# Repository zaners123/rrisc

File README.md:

# RRISC (Reduced Reduced Instruction Set Computer)

My primary goal for this project was to make a computer from "scratch"
(simple logic gates and memory, no embedded microcontrollers/FPGAs/etc) to learn more about Computer Engineering
as a "learn by doing" approach.

Since it's only made out of simple logic gates and hand-soldered, it needs to be simple in design
(no microcode/pipelining) and in implementation (trying to aim for around 50 logic chips,
none of which are more complex than a comparator).

This project includes the Assembler, LogiSim simulator/emulator, schematic, and PCB.
This is the computer at every level of abstraction, and as such this is Open Source Hardware.

## What is RISC? What does this computer do? 

A RISC computer commonly has simple operations to have higher instructions per second.
My computer has extremely simple operations to have extreme efficiency (ideally).
My goal for this computer is for it to run at about 20MHz.

This is a General Purpose Von-Neumann-Architecture computer with 8-bit instructions.
It has 64Kb of RAM and all 16 instructions follow a quick 3-stage IF/EX/WB cycle.

Instructions are broken up into two parts. Here's the entire **Instruction Set Architecture**:

 ID | Opcode |  Description           |  Argument Type
----|--------|------------------------|-------------------------
 _  | 4 bits | _                      | 4 bits
0x0 | ADD    | Add to R0              | Register(1)
0x1 | ADDI   | Add to R0              | Immediate(2)       
0x2 | SUB    | Subtract from R0       | Register(1)   
0x3 | SUBI   | Subtract from R0       | Immediate(2)  
0x4 | SKIP   | Skip next instruction  | Condition(3)  
0x5 | JUMP   | Jump to MEM            | Condition(3)  
0x6 | XOR    | Xor                    | Register(1)        
0x7 | XORI   | Xor                    | Immediate(2)       
0x8 | AND    | And                    | Register(1)        
0x9 | ANDI   | And                    | Immediate(2)       
0xA | SET    | Move ACC to Reg        | Register(1)
0xB | RB     | Read from memory to Reg| Register(1)
0xC | GET    | Move Reg to ACC        | Register(1)
0xD | WB     | Write from reg to memory|Register(1)
0xE | OR     |                        |
0xF | ORI    |                        |

## Register(1)
The last 4 bits of this argument point to one of the 16 registers.

ACC (AKA R0) is the accumulator register.

R1-RC General Purpose Registers.

RMH,RML point in memory (Register Memory High, Register Memory Low).

RCMP is used in conditional operations<sup>[3](3)</sup>

## Immediate(2)

## Condition(3)

# Assembler

Given an assembly file (Ex: code.asm), it turns it into a hex file (Ex: code.asm.hex) that can be loaded either onto
the real computer, or the simulated computer in LogiSim.

# Simulation

This represents the computer's overall layout. It is both a logical diagram for the computer and a convenient simulator for programs.

Open this with Logisim Evolution. I use "logisim-evolution-3.4.1-all.jar".
Upload the hex from the assembler into the RAM, start the controller, and watch it run!

# Hardware

The strict hardware requirement of this computer is that everything except the memory-mapped-IO has to be made from 7400 logic.

This is made in KiCad, and contains the schematic (local layout of how things connect)
and the PCB design (how to physically connect everything together).

The plan is to have the submodules used in LogiSim (registers, ALU, RAM, etc) be a daughter board for the main PCB.

The plan is to design/order/build the PCBs in this order:
1. Program Counter
    - Logic for jump/skip decisions
2. Registers
    - Might use either a literal register file (select MUX, asynchronous D-latch, 8x 16:1 demux) or a 74xx register file 
3. ALU
4. RAM/ROM/Programmer
5. Motherboard/Controller
6. Memory-Mapped IO
    - Memory Mapped UART
    - Memory Mapped 7-segment Display

This way, I can test them all separately, and revisions can be made more easily.

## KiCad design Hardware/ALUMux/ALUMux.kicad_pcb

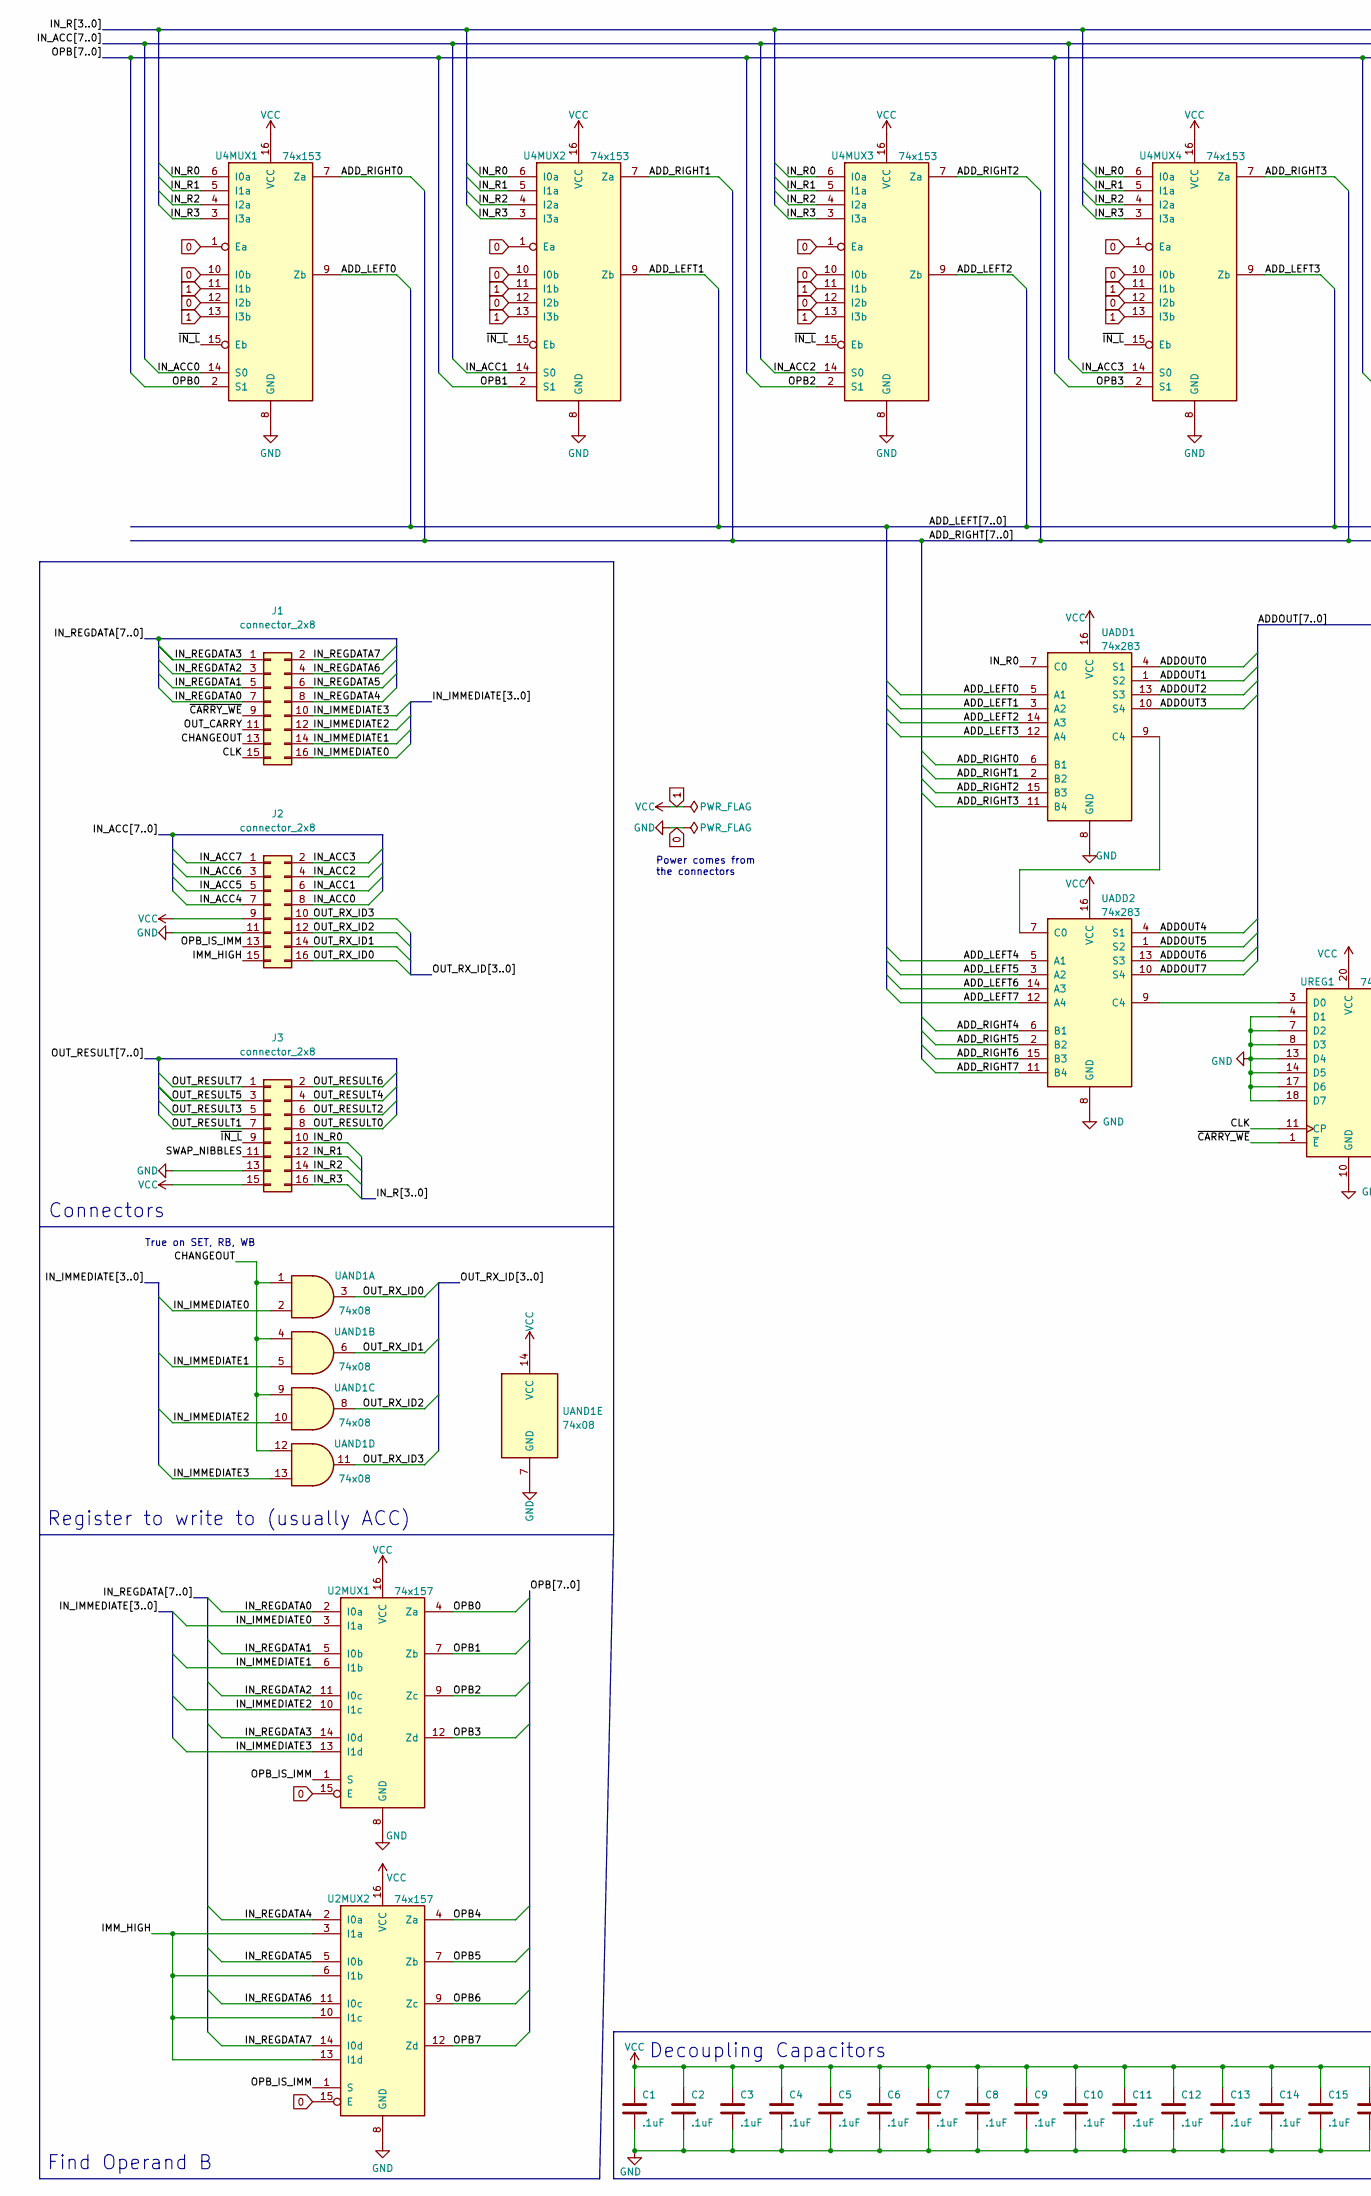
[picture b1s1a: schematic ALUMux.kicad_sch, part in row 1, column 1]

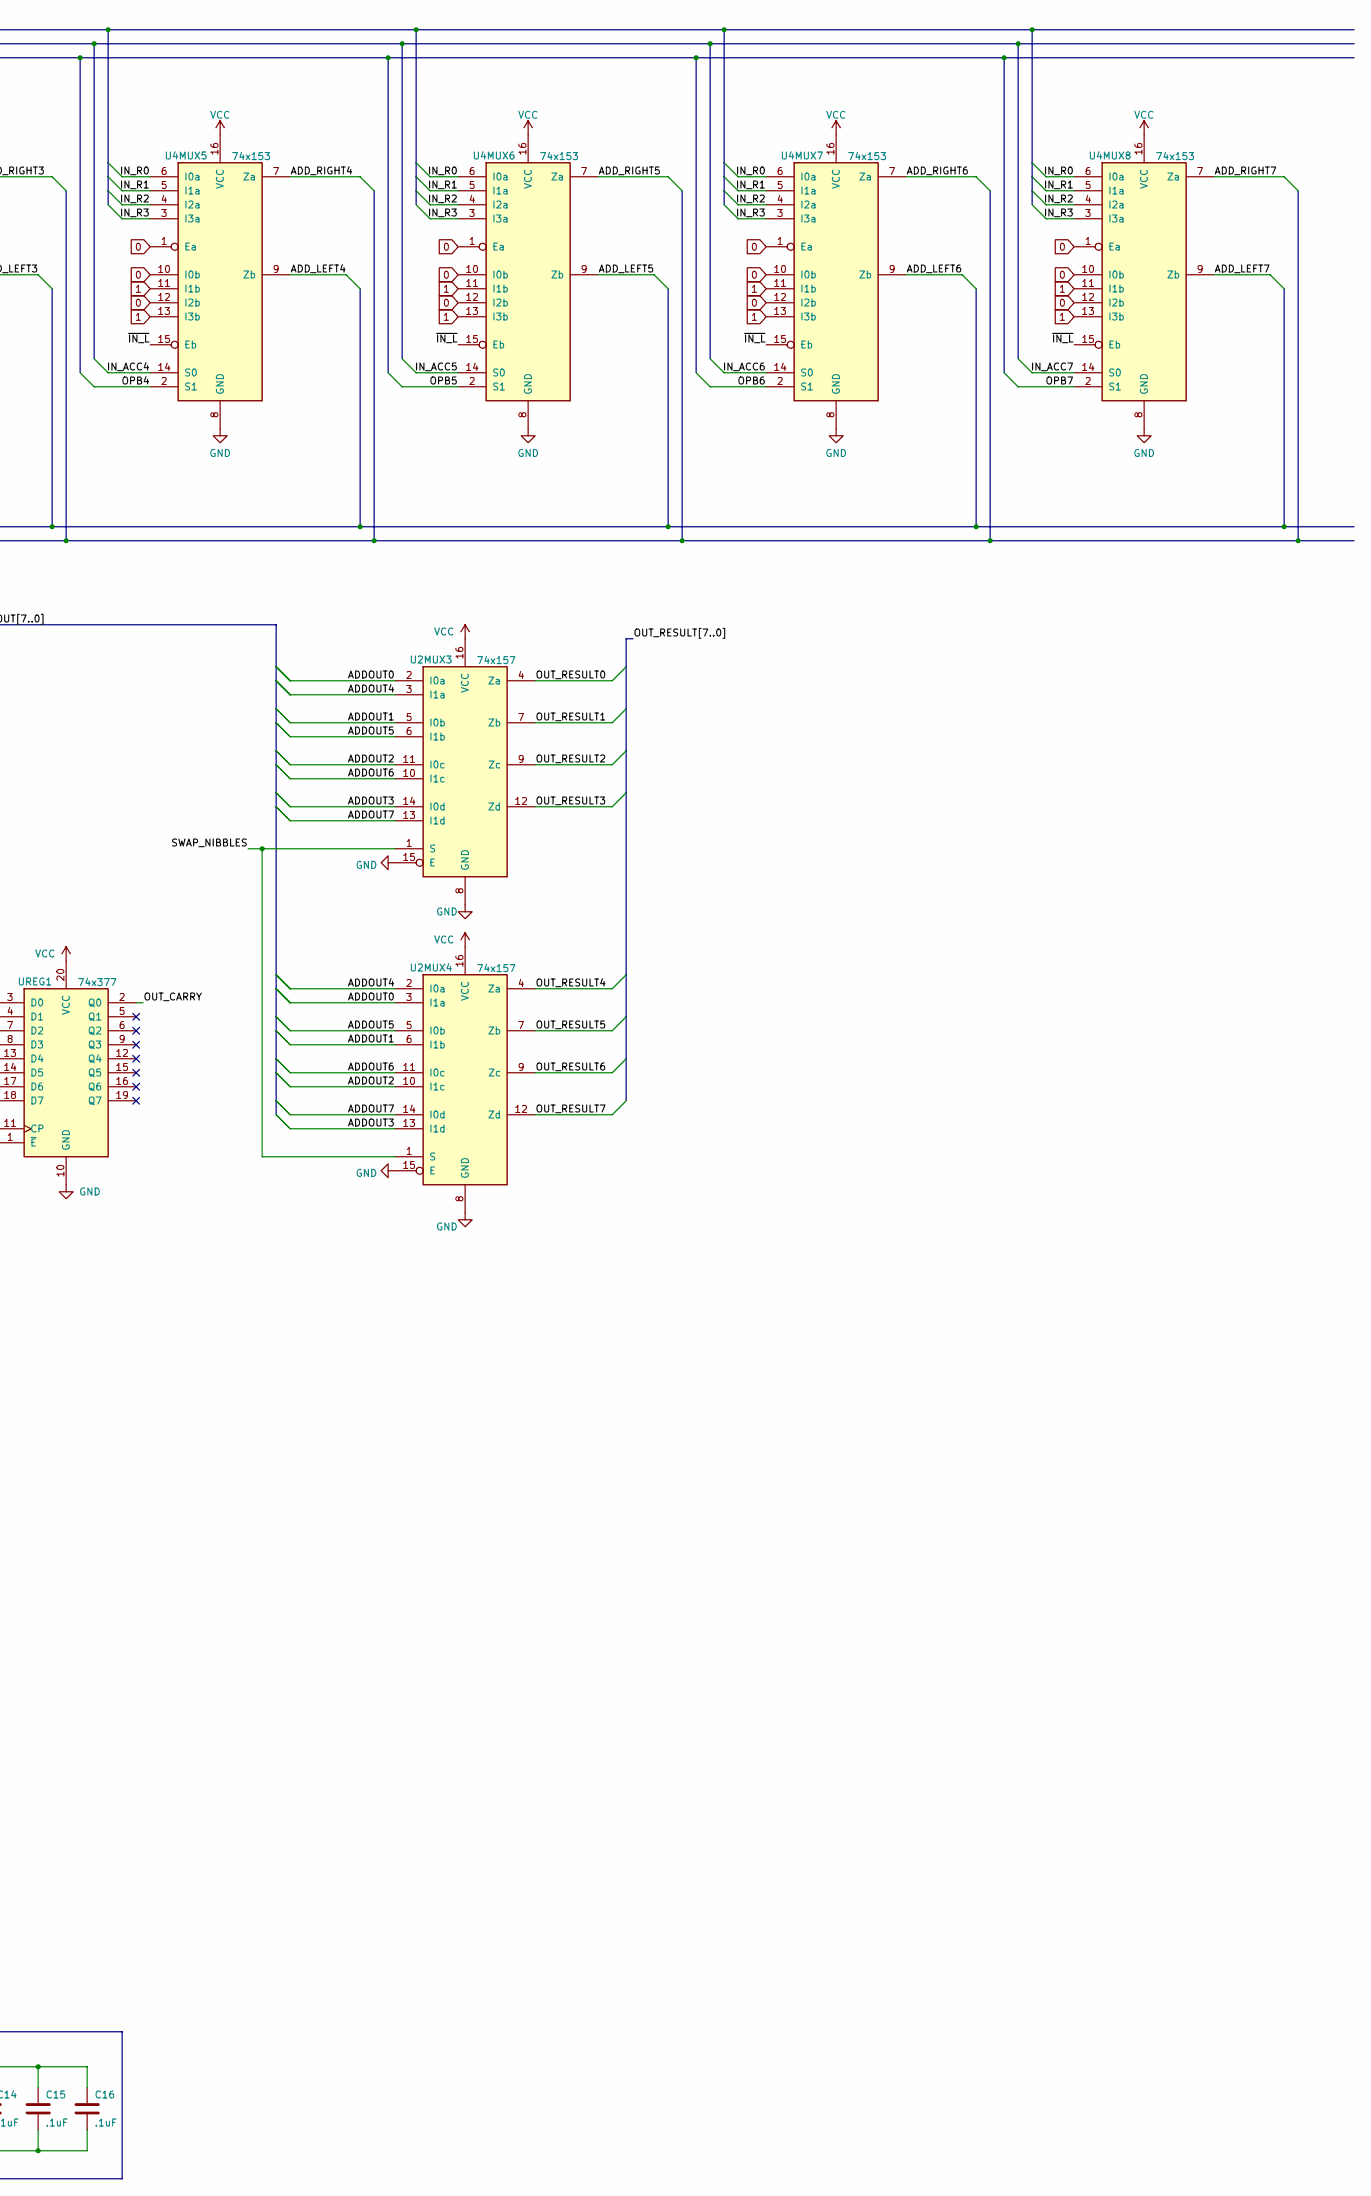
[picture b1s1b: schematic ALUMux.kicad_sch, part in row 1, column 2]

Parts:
C1, C2, C3, C4, C5, C6, C7, C8, C9, C10, C11, C12, C13, C14, C15, C16: .1uF; C_1206_3216Metric_Pad1.33x1.80mm_HandSolder
J1, J2, J3: connector_2x8; PinHeader_2x08_P2.54mm_Horizontal
U2MUX1, U2MUX2, U2MUX3, U2MUX4: 74x157; D_R-PDSO-G16
U4MUX1, U4MUX2, U4MUX3, U4MUX4, U4MUX5, U4MUX6, U4MUX7, U4MUX8: 74x153; D_R-PDSO-G16
UADD1, UADD2: 74x283; D_R-PDSO-G16
UAND1: 74x08; D_R-PDSO-G14
UREG1: 74x377; ON-SOIC20-WB

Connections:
0: C1.2, C2.2, C3.2, C4.2, C5.2, C6.2, C7.2, C8.2, C9.2, C10.2, C11.2, C12.2, C13.2, C14.2, C15.2, C16.2, J2.11, J3.13, U2MUX1.8 (GND), U2MUX1.15 (E), U2MUX2.8 (GND), U2MUX2.15 (E), U2MUX3.8 (GND), U2MUX3.15 (E), U2MUX4.8 (GND), U2MUX4.15 (E), U4MUX1.1 (Ea), U4MUX1.8 (GND), U4MUX1.10 (I0b), U4MUX1.12 (I2b), U4MUX2.1 (Ea), U4MUX2.8 (GND), U4MUX2.10 (I0b), U4MUX2.12 (I2b), U4MUX3.1 (Ea), U4MUX3.8 (GND), U4MUX3.10 (I0b), U4MUX3.12 (I2b), U4MUX4.1 (Ea), U4MUX4.8 (GND), U4MUX4.10 (I0b), U4MUX4.12 (I2b), U4MUX5.1 (Ea), U4MUX5.8 (GND), U4MUX5.10 (I0b), U4MUX5.12 (I2b), U4MUX6.1 (Ea), U4MUX6.8 (GND), U4MUX6.10 (I0b), U4MUX6.12 (I2b), U4MUX7.1 (Ea), U4MUX7.8 (GND), U4MUX7.10 (I0b), U4MUX7.12 (I2b), U4MUX8.1 (Ea), U4MUX8.8 (GND), U4MUX8.10 (I0b), U4MUX8.12 (I2b), UADD1.8 (GND), UADD2.8 (GND), UAND1.7 (GND), UREG1.4 (D1), UREG1.7 (D2), UREG1.8 (D3), UREG1.10 (GND), UREG1.13 (D4), UREG1.14 (D5), UREG1.17 (D6), UREG1.18 (D7)
1: C1.1, C2.1, C3.1, C4.1, C5.1, C6.1, C7.1, C8.1, C9.1, C10.1, C11.1, C12.1, C13.1, C14.1, C15.1, C16.1, J2.9, J3.15, U2MUX1.16 (VCC), U2MUX2.16 (VCC), U2MUX3.16 (VCC), U2MUX4.16 (VCC), U4MUX1.11 (I1b), U4MUX1.13 (I3b), U4MUX1.16 (VCC), U4MUX2.11 (I1b), U4MUX2.13 (I3b), U4MUX2.16 (VCC), U4MUX3.11 (I1b), U4MUX3.13 (I3b), U4MUX3.16 (VCC), U4MUX4.11 (I1b), U4MUX4.13 (I3b), U4MUX4.16 (VCC), U4MUX5.11 (I1b), U4MUX5.13 (I3b), U4MUX5.16 (VCC), U4MUX6.11 (I1b), U4MUX6.13 (I3b), U4MUX6.16 (VCC), U4MUX7.11 (I1b), U4MUX7.13 (I3b), U4MUX7.16 (VCC), U4MUX8.11 (I1b), U4MUX8.13 (I3b), U4MUX8.16 (VCC), UADD1.16 (VCC), UADD2.16 (VCC), UAND1.14 (VCC), UREG1.20 (VCC)
/ADDOUT0: U2MUX3.2 (I0a), U2MUX4.3 (I1a), UADD1.4 (S1)
/ADDOUT1: U2MUX3.5 (I0b), U2MUX4.6 (I1b), UADD1.1 (S2)
/ADDOUT2: U2MUX3.11 (I0c), U2MUX4.10 (I1c), UADD1.13 (S3)
/ADDOUT3: U2MUX3.14 (I0d), U2MUX4.13 (I1d), UADD1.10 (S4)
/ADDOUT4: U2MUX3.3 (I1a), U2MUX4.2 (I0a), UADD2.4 (S1)
/ADDOUT5: U2MUX3.6 (I1b), U2MUX4.5 (I0b), UADD2.1 (S2)
/ADDOUT6: U2MUX3.10 (I1c), U2MUX4.11 (I0c), UADD2.13 (S3)
/ADDOUT7: U2MUX3.13 (I1d), U2MUX4.14 (I0d), UADD2.10 (S4)
/ADD_LEFT0: U4MUX1.9 (Zb), UADD1.5 (A1)
/ADD_LEFT1: U4MUX2.9 (Zb), UADD1.3 (A2)
/ADD_LEFT2: U4MUX3.9 (Zb), UADD1.14 (A3)
/ADD_LEFT3: U4MUX4.9 (Zb), UADD1.12 (A4)
/ADD_LEFT4: U4MUX5.9 (Zb), UADD2.5 (A1)
/ADD_LEFT5: U4MUX6.9 (Zb), UADD2.3 (A2)
/ADD_LEFT6: U4MUX7.9 (Zb), UADD2.14 (A3)
/ADD_LEFT7: U4MUX8.9 (Zb), UADD2.12 (A4)
/ADD_RIGHT0: U4MUX1.7 (Za), UADD1.6 (B1)
/ADD_RIGHT1: U4MUX2.7 (Za), UADD1.2 (B2)
/ADD_RIGHT2: U4MUX3.7 (Za), UADD1.15 (B3)
/ADD_RIGHT3: U4MUX4.7 (Za), UADD1.11 (B4)
/ADD_RIGHT4: U4MUX5.7 (Za), UADD2.6 (B1)
/ADD_RIGHT5: U4MUX6.7 (Za), UADD2.2 (B2)
/ADD_RIGHT6: U4MUX7.7 (Za), UADD2.15 (B3)
/ADD_RIGHT7: U4MUX8.7 (Za), UADD2.11 (B4)
/CHANGEOUT: J1.13, UAND1.1, UAND1.4, UAND1.9, UAND1.12
/CLK: J1.15, UREG1.11 (CP)
/IMM_HIGH: J2.15, U2MUX2.3 (I1a), U2MUX2.6 (I1b), U2MUX2.10 (I1c), U2MUX2.13 (I1d)
/IN_ACC0: J2.8, U4MUX1.14 (S0)
/IN_ACC1: J2.6, U4MUX2.14 (S0)
/IN_ACC2: J2.4, U4MUX3.14 (S0)
/IN_ACC3: J2.2, U4MUX4.14 (S0)
/IN_ACC4: J2.7, U4MUX5.14 (S0)
/IN_ACC5: J2.5, U4MUX6.14 (S0)
/IN_ACC6: J2.3, U4MUX7.14 (S0)
/IN_ACC7: J2.1, U4MUX8.14 (S0)
/IN_IMMEDIATE0: J1.16, U2MUX1.3 (I1a), UAND1.2
/IN_IMMEDIATE1: J1.14, U2MUX1.6 (I1b), UAND1.5
/IN_IMMEDIATE2: J1.12, U2MUX1.10 (I1c), UAND1.10
/IN_IMMEDIATE3: J1.10, U2MUX1.13 (I1d), UAND1.13
/IN_R0: J3.10, U4MUX1.6 (I0a), U4MUX2.6 (I0a), U4MUX3.6 (I0a), U4MUX4.6 (I0a), U4MUX5.6 (I0a), U4MUX6.6 (I0a), U4MUX7.6 (I0a), U4MUX8.6 (I0a), UADD1.7 (C0)
/IN_R1: J3.12, U4MUX1.5 (I1a), U4MUX2.5 (I1a), U4MUX3.5 (I1a), U4MUX4.5 (I1a), U4MUX5.5 (I1a), U4MUX6.5 (I1a), U4MUX7.5 (I1a), U4MUX8.5 (I1a)
/IN_R2: J3.14, U4MUX1.4 (I2a), U4MUX2.4 (I2a), U4MUX3.4 (I2a), U4MUX4.4 (I2a), U4MUX5.4 (I2a), U4MUX6.4 (I2a), U4MUX7.4 (I2a), U4MUX8.4 (I2a)
/IN_R3: J3.16, U4MUX1.3 (I3a), U4MUX2.3 (I3a), U4MUX3.3 (I3a), U4MUX4.3 (I3a), U4MUX5.3 (I3a), U4MUX6.3 (I3a), U4MUX7.3 (I3a), U4MUX8.3 (I3a)
/IN_REGDATA0: J1.7, U2MUX1.2 (I0a)
/IN_REGDATA1: J1.5, U2MUX1.5 (I0b)
/IN_REGDATA2: J1.3, U2MUX1.11 (I0c)
/IN_REGDATA3: J1.1, U2MUX1.14 (I0d)
/IN_REGDATA4: J1.8, U2MUX2.2 (I0a)
/IN_REGDATA5: J1.6, U2MUX2.5 (I0b)
/IN_REGDATA6: J1.4, U2MUX2.11 (I0c)
/IN_REGDATA7: J1.2, U2MUX2.14 (I0d)
/OPB0: U2MUX1.4 (Za), U4MUX1.2 (S1)
/OPB1: U2MUX1.7 (Zb), U4MUX2.2 (S1)
/OPB2: U2MUX1.9 (Zc), U4MUX3.2 (S1)
/OPB3: U2MUX1.12 (Zd), U4MUX4.2 (S1)
/OPB4: U2MUX2.4 (Za), U4MUX5.2 (S1)
/OPB5: U2MUX2.7 (Zb), U4MUX6.2 (S1)
/OPB6: U2MUX2.9 (Zc), U4MUX7.2 (S1)
/OPB7: U2MUX2.12 (Zd), U4MUX8.2 (S1)
/OPB_IS_IMM: J2.13, U2MUX1.1 (S), U2MUX2.1 (S)
/OUT_CARRY: J1.11, UREG1.2 (Q0)
/OUT_RESULT0: J3.8, U2MUX3.4 (Za)
/OUT_RESULT1: J3.7, U2MUX3.7 (Zb)
/OUT_RESULT2: J3.6, U2MUX3.9 (Zc)
/OUT_RESULT3: J3.5, U2MUX3.12 (Zd)
/OUT_RESULT4: J3.4, U2MUX4.4 (Za)
/OUT_RESULT5: J3.3, U2MUX4.7 (Zb)
/OUT_RESULT6: J3.2, U2MUX4.9 (Zc)
/OUT_RESULT7: J3.1, U2MUX4.12 (Zd)
/OUT_RX_ID0: J2.16, UAND1.3
/OUT_RX_ID1: J2.14, UAND1.6
/OUT_RX_ID2: J2.12, UAND1.8
/OUT_RX_ID3: J2.10, UAND1.11
/SWAP_NIBBLES: J3.11, U2MUX3.1 (S), U2MUX4.1 (S)
/~CARRY_WE: J1.9, UREG1.1 (~E)
/~IN_L: J3.9, U4MUX1.15 (Eb), U4MUX2.15 (Eb), U4MUX3.15 (Eb), U4MUX4.15 (Eb), U4MUX5.15 (Eb), U4MUX6.15 (Eb), U4MUX7.15 (Eb), U4MUX8.15 (Eb)
unnamed: UADD1.9 (C4), UADD2.7 (C0)
unnamed: UADD2.9 (C4), UREG1.3 (D0)

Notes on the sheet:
Connectors
True on SET, RB, WB
Register to write to (usually ACC)
Power comes from the connectors
Find Operand B
Decoupling Capacitors

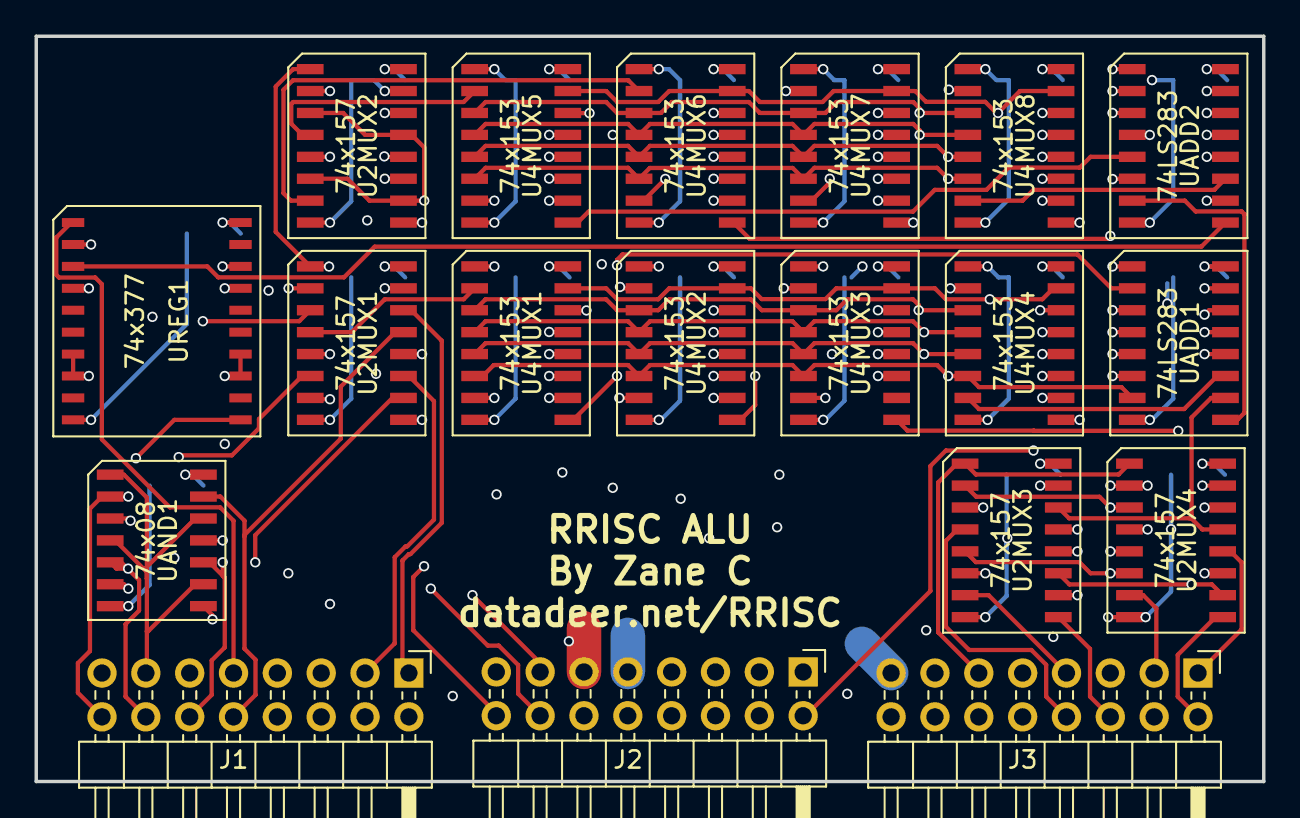
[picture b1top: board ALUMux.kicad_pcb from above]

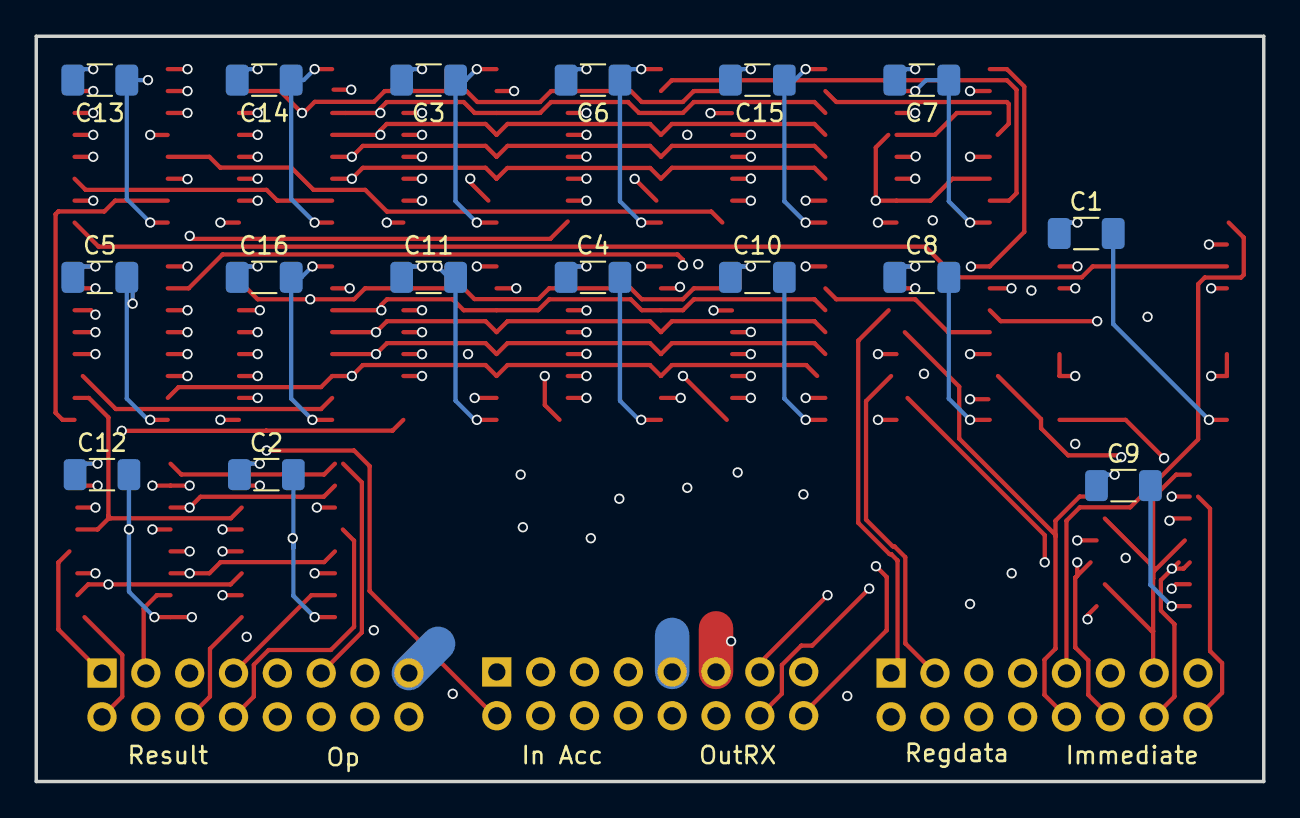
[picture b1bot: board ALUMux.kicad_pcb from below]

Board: 4 copper layers, 71.1 x 43.2 mm, 35 parts (16 on the bottom side), 80 nets.

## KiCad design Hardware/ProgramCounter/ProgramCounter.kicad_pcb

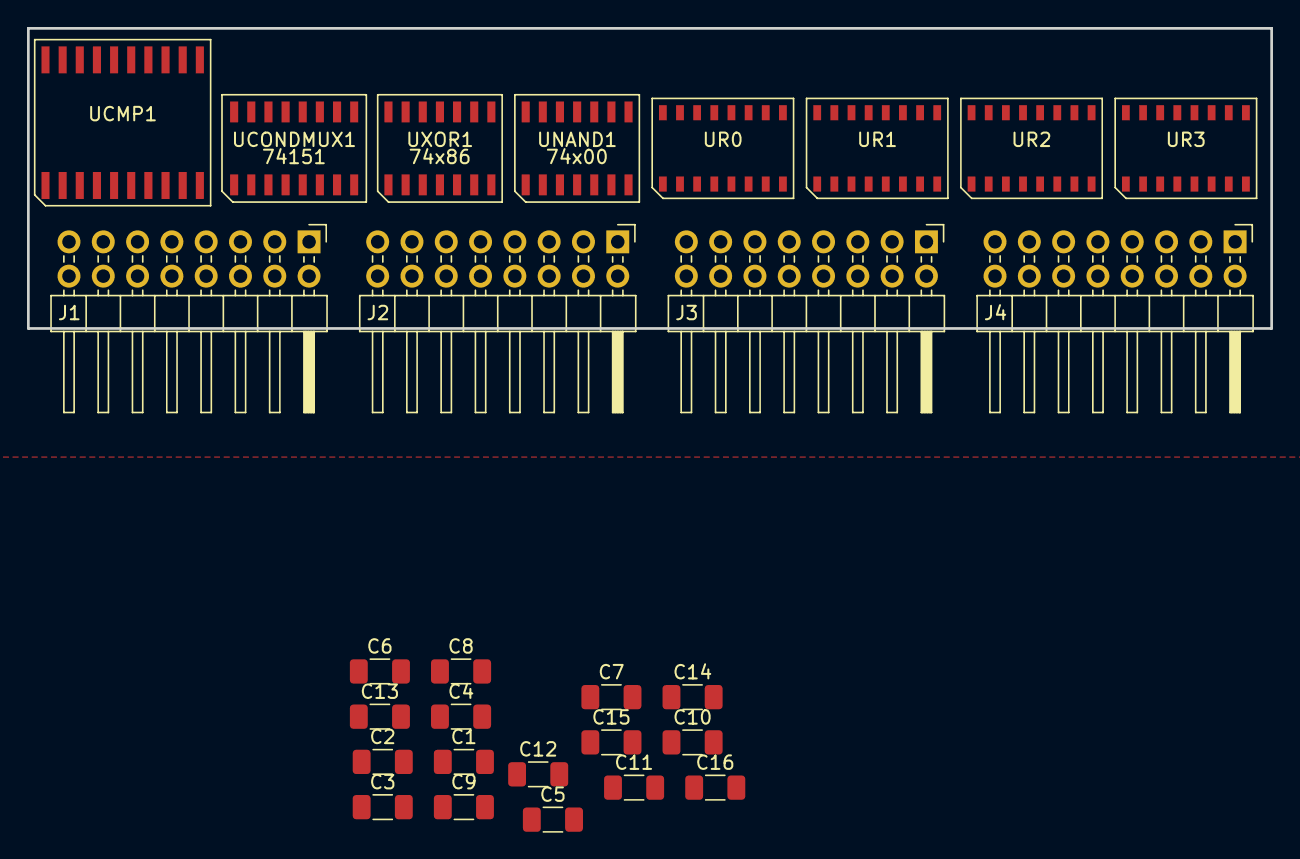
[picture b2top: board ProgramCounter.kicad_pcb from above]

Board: 4 copper layers, 92.1 x 22.2 mm, 28 parts (0 on the bottom side), 70 nets, no tracks yet.

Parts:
C1, C2, C3, C4, C5, C6, C7, C8, C9, C10, C11, C12, C13, C14, C15, C16: .1uF; C_1206_3216Metric_Pad1.33x1.80mm_HandSolder
J1, J2, J3, J4: Conn_02x08; PinHeader_2x08_P2.54mm_Horizontal
UCMP1: 74LS684; SOIC20_TI_DW0020A
UCONDMUX1: 74151; D_R-PDSO-G16
UNAND1: 74x00; D_R-PDSO-G14
UR0, UR1, UR2, UR3: 74LS161; SOIC16-ONSEMI_751B-05_K
UXOR1: 74x86; D_R-PDSO-G14

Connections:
/CARRY0: UR0.15 (TC), UR1.10 (CET)
/CARRY1: UR1.15 (TC), UR2.10 (CET)
/CARRY2: UR2.15 (TC), UR3.10 (CET)
/CEP: J2.16, UR0.7 (CEP), UR1.7 (CEP), UR2.7 (CEP), UR3.7 (CEP)
/CLK_WB: J2.8, UR0.2 (CP), UR1.2 (CP), UR2.2 (CP), UR3.2 (CP)
/FLAG_CARRY: J2.11, UCONDMUX1.12 (I7)
/IMM0: J2.3, UXOR1.1
/IMM1: J2.5, UCONDMUX1.11 (S0)
/IMM2: J2.7, UCONDMUX1.10 (S1)
/IMM3: J2.9, UCONDMUX1.9 (S2)
/IS_SKIP: J2.10, UNAND1.8
/JINST: J2.14, UNAND1.13
/PCEVENT: UNAND1.4, UNAND1.12, UXOR1.3
/PCOUT0: J3.16, UR0.14 (Q0)
/PCOUT1: J3.14, UR0.13 (Q1)
/PCOUT2: J3.12, UR0.12 (Q2)
/PCOUT3: J3.10, UR0.11 (Q3)
/PCOUT4: J3.8, UR1.14 (Q0)
/PCOUT5: J3.6, UR1.13 (Q1)
/PCOUT6: J3.4, UR1.12 (Q2)
/PCOUT7: J3.2, UR1.11 (Q3)
/PCOUT8: J4.16, UR2.14 (Q0)
/PCOUT9: J4.14, UR2.13 (Q1)
/PCOUT10: J4.12, UR2.12 (Q2)
/PCOUT11: J4.10, UR2.11 (Q3)
/PCOUT12: J4.8, UR3.14 (Q0)
/PCOUT13: J4.6, UR3.13 (Q1)
/PCOUT14: J4.4, UR3.12 (Q2)
/PCOUT15: J4.2, UR3.11 (Q3)
/RCD0: J1.1, UCMP1.3 (Q0)
/RCD1: J1.3, UCMP1.5 (Q1)
/RCD2: J1.5, UCMP1.7 (Q2)
/RCD3: J1.7, UCMP1.9 (Q3)
/RCD4: J1.9, UCMP1.12 (Q4)
/RCD5: J1.11, UCMP1.14 (Q5)
/RCD6: J1.13, UCMP1.16 (Q6)
/RCD7: J1.15, UCMP1.18 (Q7)
/RCS0: J1.2, UCMP1.2 (P0), UCONDMUX1.13 (I6)
/RCS1: J1.4, UCMP1.4 (P1)
/RCS2: J1.6, UCMP1.6 (P2)
/RCS3: J1.8, UCMP1.8 (P3)
/RCS4: J1.10, UCMP1.11 (P4)
/RCS5: J1.12, UCMP1.13 (P5)
/RCS6: J1.14, UCMP1.15 (P6)
/RCS7: J1.16, UCMP1.17 (P7), UCONDMUX1.2 (I2)
/REGMEM0: J3.15, UR0.3 (D0)
/REGMEM1: J3.13, UR0.4 (D1)
/REGMEM2: J3.11, UR0.5 (D2)
/REGMEM3: J3.9, UR0.6 (D3)
/REGMEM4: J3.7, UR1.3 (D0)
/REGMEM5: J3.5, UR1.4 (D1)
/REGMEM6: J3.3, UR1.5 (D2)
/REGMEM7: J3.1, UR1.6 (D3)
/REGMEM8: J4.15, UR2.3 (D0)
/REGMEM9: J4.13, UR2.4 (D1)
/REGMEM10: J4.11, UR2.5 (D2)
/REGMEM11: J4.9, UR2.6 (D3)
/REGMEM12: J4.7, UR3.3 (D0)
/REGMEM13: J4.5, UR3.4 (D1)
/REGMEM14: J4.3, UR3.5 (D2)
/REGMEM15: J4.1, UR3.6 (D3)
/SINST: J2.12, UNAND1.5
/cmpeq: UCMP1.19 (~P=Q), UCONDMUX1.15 (I4), UNAND1.1
/cmpgt: UCMP1.1 (~P>Q), UCONDMUX1.1 (I3), UNAND1.2
/~IS_JMP: UNAND1.11, UR0.9 (~PE), UR1.9 (~PE), UR2.9 (~PE), UR3.9 (~PE)
/~IS_SKIP: UNAND1.6, UNAND1.9
/~RST: J2.6, UR0.1 (~MR), UR1.1 (~MR), UR2.1 (~MR), UR3.1 (~MR)
GND: C1.2, C2.2, C3.2, C4.2, C5.2, C6.2, C7.2, C8.2, C9.2, C10.2, C11.2, C12.2, C13.2, C14.2, C15.2, C16.2, J2.1, J2.2, J2.15, UCMP1.10 (Gnd), UCONDMUX1.4 (I0), UCONDMUX1.7 (~E), UCONDMUX1.8 (GND), UNAND1.7 (GND), UR0.8 (GND), UR1.8 (GND), UR2.8 (GND), UR3.8 (GND), UXOR1.4, UXOR1.5, UXOR1.7 (GND), UXOR1.9, UXOR1.10, UXOR1.12, UXOR1.13
unnamed: UCONDMUX1.5 (Q), UXOR1.2
VCC: C1.1, C2.1, C3.1, C4.1, C5.1, C6.1, C7.1, C8.1, C9.1, C10.1, C11.1, C12.1, C13.1, C14.1, C15.1, C16.1, J2.4, J2.13, UCMP1.20 (Vcc), UCONDMUX1.16 (VCC), UNAND1.10, UNAND1.14 (VCC), UR0.10 (CET), UR0.16 (VCC), UR1.16 (VCC), UR2.16 (VCC), UR3.16 (VCC), UXOR1.14 (VCC)
